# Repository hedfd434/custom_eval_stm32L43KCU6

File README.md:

# Custom evaluation board for stm32L432KCU6

This is a project of the custom evalution board for stm32L432KCU6.
The eval board was created for future test and prototypin during "2025/26 can-sat 🛰️ competition" organisated by ESA 🇪🇺 (European Space Agency), simultaneously it is a part of our PDR report 📑 (Preeliminary Desing Report).
By creating this board we want to show our capabilities in terms of electronics manufacturing ⚡📟.

<div style="display: flex; justify-content: center; gap: 20px;">
  <figure>
    
    <figcaption style="text-align: center;">Logo of my team "Crius SPACE"</figcaption>
  </figure>
  <figure>
    
    <figcaption style="text-align: center;">We are taking part in can-sat competition by ESA</figcaption>
  </figure>
</div>

<div style="display: flex; justify-content: center; gap: 20px;">
  <figure>
    
    <figcaption style="text-align: center;">Real images of soldered board (running code)</figcaption>
  </figure>
  <figure>
    
    <figcaption style="text-align: center;">Render of the board in KiCAD</figcaption>
  </figure>
</div>

## future improvements, known issues and thing which are not tested
### known issues ⚠️❗:
- missing labels  - ()

- too small package - the capacitors for the LSE (Y2) are in size of 0402, (especially during manual soldering using hot-air gun or either conventional soldering iron (0603 is ratiobale limit for the size))

- space usage - board is bigger than the most popular eval boards like "blue/black pill" ❗

### probabable issues (not tested) ⚠️❗:
- reversd ESD protection for the usb (it is not necessary to use it)

### future improvements 📈🚀:
- components - no smaller than 0603 for manual soldering

- silk layer labels - complete silk layer labels

## customisation options ⚙️🛠️:
- as you can see on the photos of the real not everything is soldered:
1. 0ohm reistor on every diode - it allows you to reduce power usage in battery base aplications 🔋🪫.

2. 0ohm resistors on signal pins for usb - allows user to use pins in 2 different ways.

3. extra user button - with pull-up resistor and place for anit-debounce capacitor.

## extra files 📂:
1. stm32l432kcu6_eval_part_list.csv - file which contains list of the used elements with quantities for 1 board.

2. documentation folder - (in progress) folder which contains documentation for every component used in the project.

3. production_file_1.zip and production_file_1 - production ready files with current version of the project

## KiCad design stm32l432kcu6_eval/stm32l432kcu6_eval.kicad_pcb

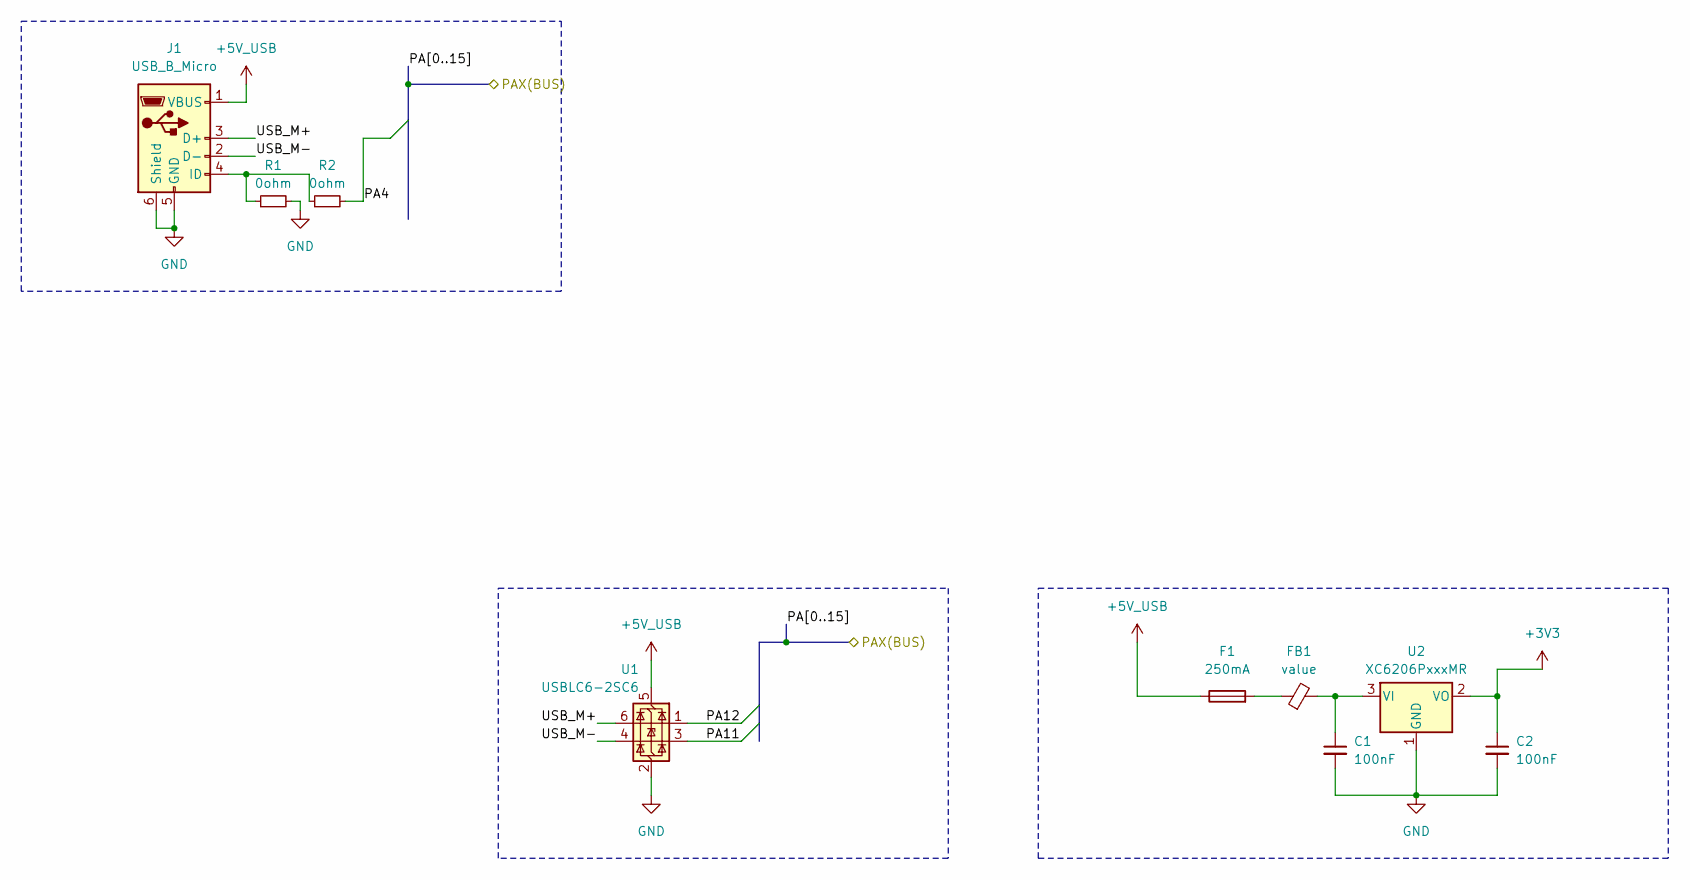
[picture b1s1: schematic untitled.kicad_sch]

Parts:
C1, C2: 100nF; C_0603_1608Metric
F1: 250mA; Fuse_0603_1608Metric
FB1: value; L_0603_1608Metric
J1: USB_B_Micro; USB_Micro-B_Molex-105017-0001
R1, R2: 0ohm; R_0603_1608Metric
U1: USBLC6-2SC6; SOT-23-6
U2: XC6206PxxxMR; SOT-23-3

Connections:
+3V3: C2.1, U2.2 (VO); also elsewhere on the board
+5V_USB: F1.1, J1.1 (VBUS), U1.5 (VBUS); also elsewhere on the board
/connectors_gpios_2_5_4/PA4: R2.2; also elsewhere on the board
/connectors_gpios_2_5_4/PA11: U1.3 (I/O2); also elsewhere on the board
/connectors_gpios_2_5_4/PA12: U1.1 (I/O1); also elsewhere on the board
/power_usb/USB_M+: J1.3 (D+), U1.6 (I/O1)
/power_usb/USB_M-: J1.2 (D-), U1.4 (I/O2)
GND: C1.2, C2.2, J1.5 (GND), J1.6 (Shield), R1.2, U1.2 (GND), U2.1 (GND); also elsewhere on the board
unnamed: F1.2, FB1.1
unnamed: J1.4 (ID), R1.1, R2.1
unnamed: C1.1, FB1.2, U2.3 (VI)

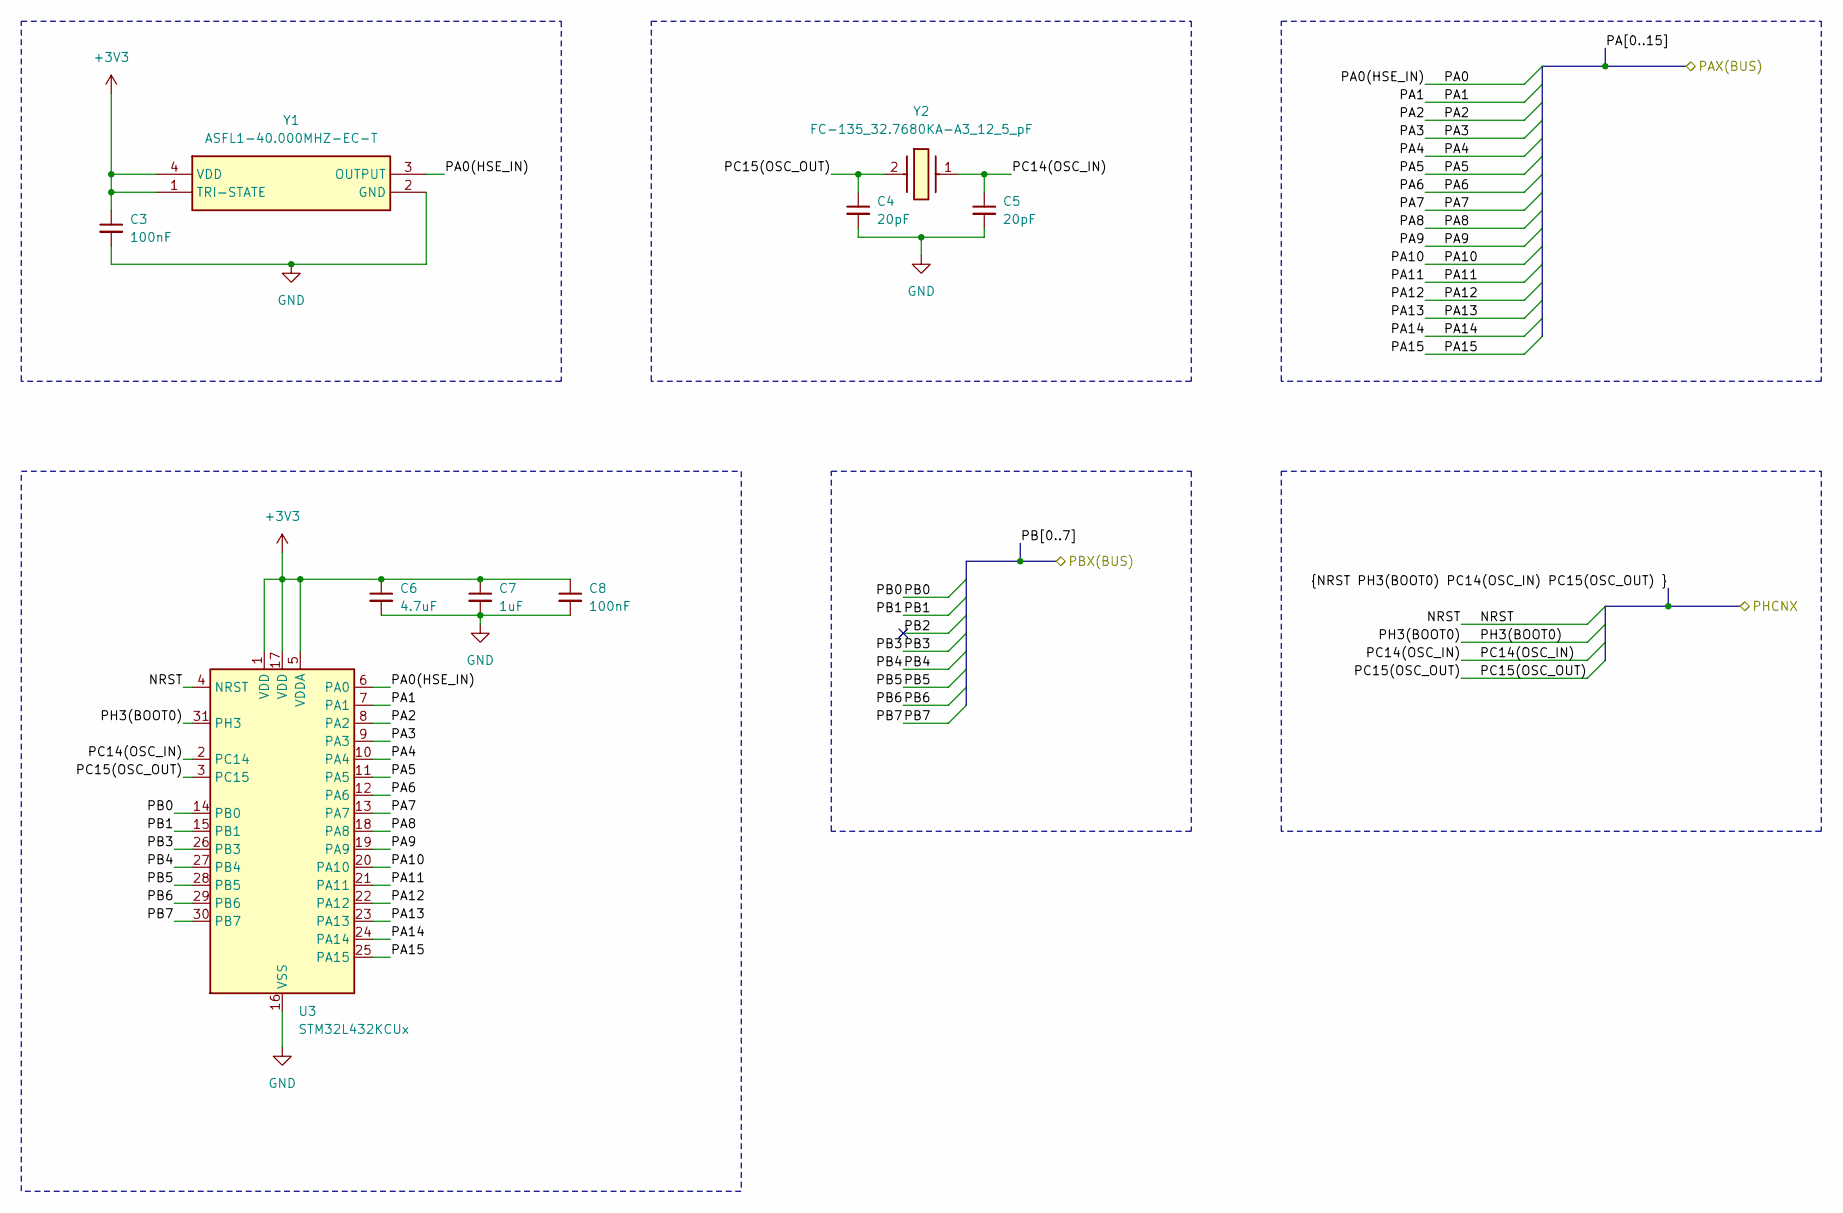
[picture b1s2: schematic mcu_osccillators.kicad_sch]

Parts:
C3, C8: 100nF; C_0603_1608Metric
C4, C5: 20pF; C_0402_1005Metric
C6: 4.7uF; C_0603_1608Metric
C7: 1uF; C_0603_1608Metric
U3: STM32L432KCUx; QFN-32-1EP_5x5mm_P0.5mm_EP3.65x3.65mm_ThermalVias
Y1: ASFL1-40.000MHZ-EC-T; ASFL1; Mouser Part Number 815-ASFL1-40.0-EC-T
Y2: FC-135_32.7680KA-A3_12_5_pF; FC-135_32_7680KA-A3; Mouser Part Number 732-FC135-32.76KAA3

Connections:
+3V3: C3.1, C6.1, C7.1, C8.1, U3.1 (VDD), U3.5 (VDDA), U3.17 (VDD), Y1.1 (TRI-STATE), Y1.4 (VDD); also elsewhere on the board
/connectors_gpios_2_5_4/NRST: U3.4 (NRST); also elsewhere on the board
/connectors_gpios_2_5_4/PA0: U3.6 (PA0), Y1.3 (OUTPUT); also elsewhere on the board
/connectors_gpios_2_5_4/PA1: U3.7 (PA1); also elsewhere on the board
/connectors_gpios_2_5_4/PA2: U3.8 (PA2); also elsewhere on the board
/connectors_gpios_2_5_4/PA3: U3.9 (PA3); also elsewhere on the board
/connectors_gpios_2_5_4/PA4: U3.10 (PA4); also elsewhere on the board
/connectors_gpios_2_5_4/PA5: U3.11 (PA5); also elsewhere on the board
/connectors_gpios_2_5_4/PA6: U3.12 (PA6); also elsewhere on the board
/connectors_gpios_2_5_4/PA7: U3.13 (PA7); also elsewhere on the board
/connectors_gpios_2_5_4/PA8: U3.18 (PA8); also elsewhere on the board
/connectors_gpios_2_5_4/PA9: U3.19 (PA9); also elsewhere on the board
/connectors_gpios_2_5_4/PA10: U3.20 (PA10); also elsewhere on the board
/connectors_gpios_2_5_4/PA11: U3.21 (PA11); also elsewhere on the board
/connectors_gpios_2_5_4/PA12: U3.22 (PA12); also elsewhere on the board
/connectors_gpios_2_5_4/PA13: U3.23 (PA13); also elsewhere on the board
/connectors_gpios_2_5_4/PA14: U3.24 (PA14); also elsewhere on the board
/connectors_gpios_2_5_4/PA15: U3.25 (PA15); also elsewhere on the board
/connectors_gpios_2_5_4/PB0: U3.14 (PB0); also elsewhere on the board
/connectors_gpios_2_5_4/PB1: U3.15 (PB1); also elsewhere on the board
/connectors_gpios_2_5_4/PB3: U3.26 (PB3); also elsewhere on the board
/connectors_gpios_2_5_4/PB4: U3.27 (PB4); also elsewhere on the board
/connectors_gpios_2_5_4/PB5: U3.28 (PB5); also elsewhere on the board
/connectors_gpios_2_5_4/PB6: U3.29 (PB6); also elsewhere on the board
/connectors_gpios_2_5_4/PB7: U3.30 (PB7); also elsewhere on the board
/connectors_gpios_2_5_4/PC14(OSC_IN): C5.1, U3.2 (PC14), Y2.1; also elsewhere on the board
/connectors_gpios_2_5_4/PC15(OSC_OUT): C4.1, U3.3 (PC15), Y2.2 (X2); also elsewhere on the board
/connectors_gpios_2_5_4/PH3(BOOT0): U3.31 (PH3); also elsewhere on the board
GND: C3.2, C4.2, C5.2, C6.2, C7.2, C8.2, U3.16 (VSS), U3.32 (VSS), U3.33 (VSS), Y1.2 (GND); also elsewhere on the board

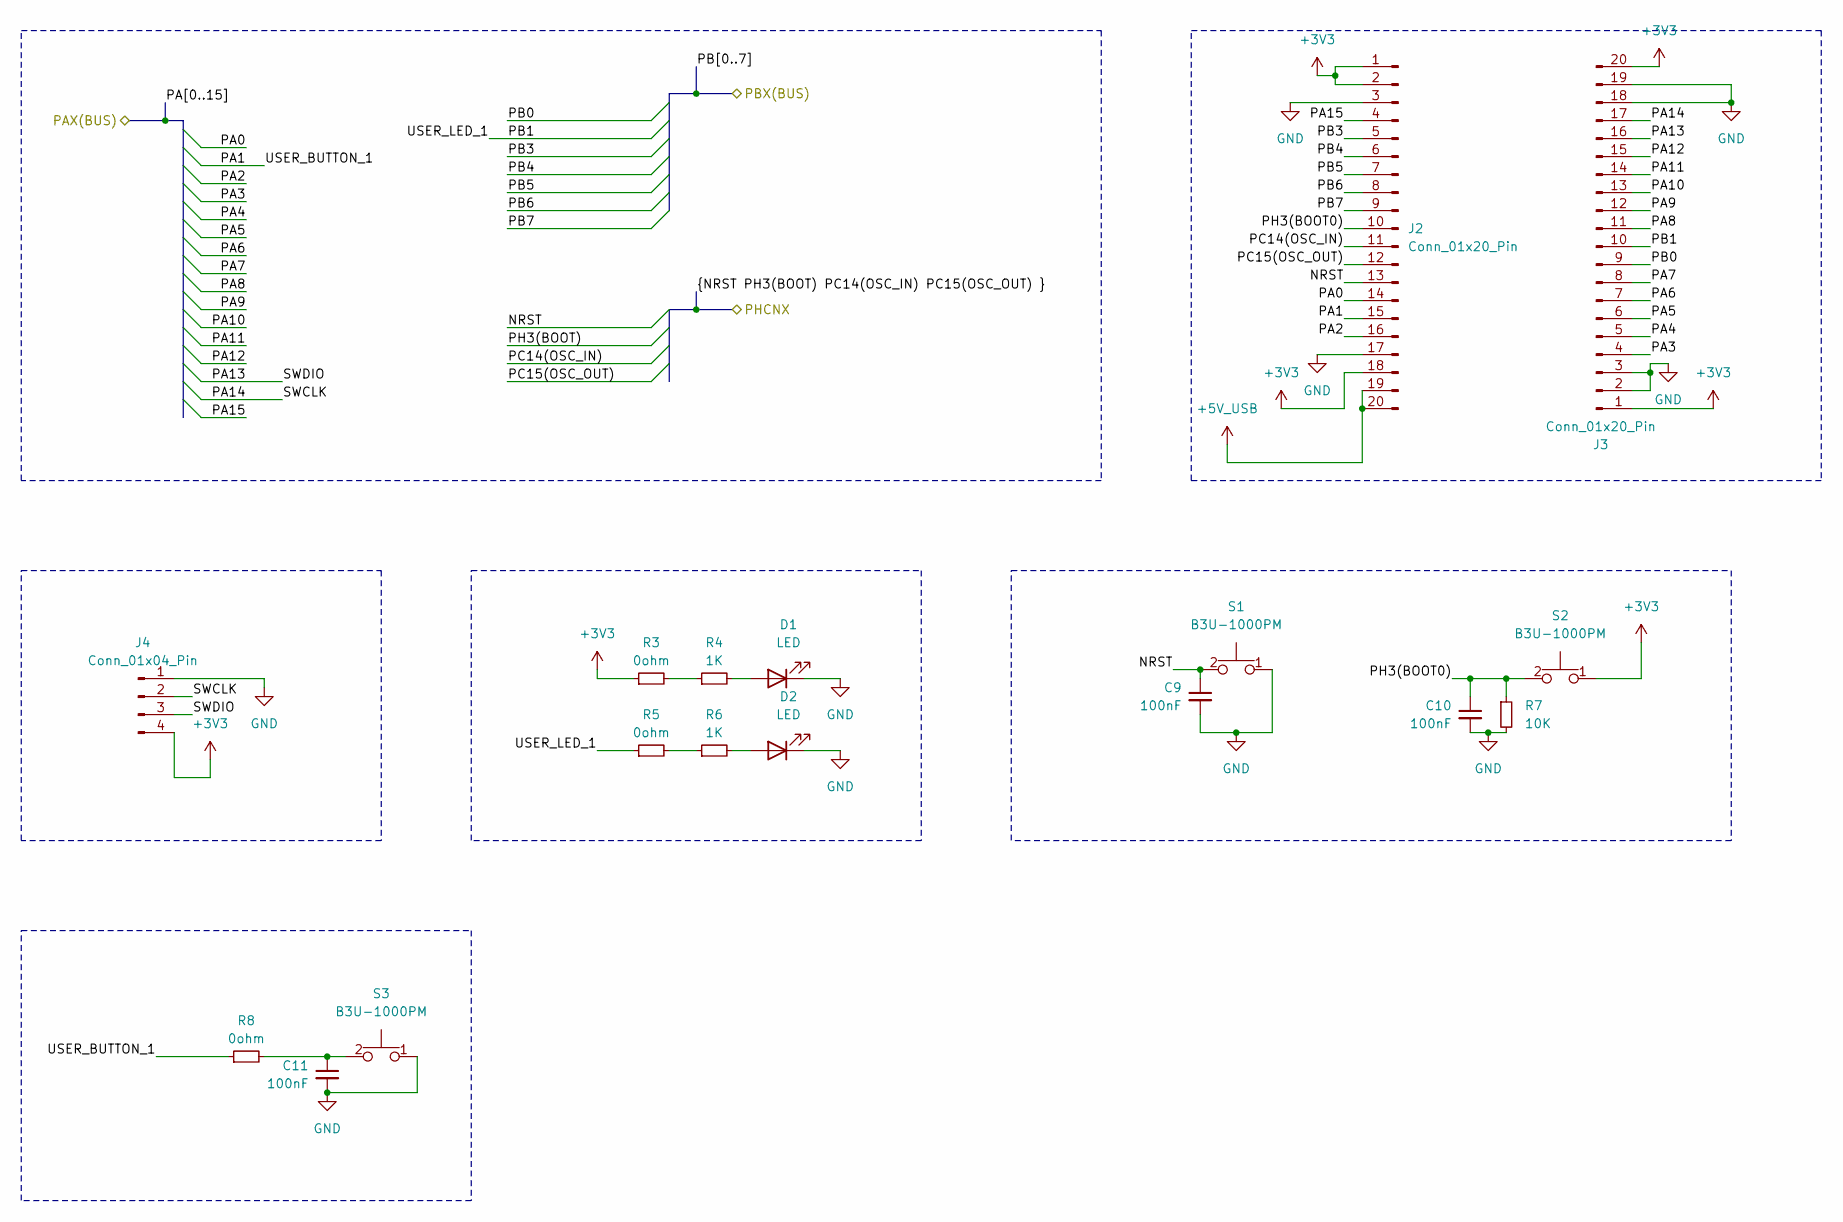
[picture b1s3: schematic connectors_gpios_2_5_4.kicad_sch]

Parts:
C9, C10, C11: 100nF; C_0603_1608Metric
D1, D2: LED; LED_0603_1608Metric
J2, J3: Conn_01x20_Pin; PinHeader_1x20_P2.54mm_Vertical
J4: Conn_01x04_Pin; PinHeader_1x04_P2.54mm_Horizontal
R3, R5, R8: 0ohm; R_0603_1608Metric
R4, R6: 1K; R_0603_1608Metric
R7: 10K; R_0603_1608Metric
S1, S2, S3: B3U-1000PM; B3U1000PM_3D_MODEL; Manufacturer_Part_Number B3U-1000PM

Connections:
+3V3: J2.1, J2.2, J2.18, J3.1, J3.20, J4.4, R3.1, S2.1; also elsewhere on the board
+5V_USB: J2.19, J2.20; also elsewhere on the board
/connectors_gpios_2_5_4/NRST: C9.1, J2.13, S1.2; also elsewhere on the board
/connectors_gpios_2_5_4/PA0: J2.14; also elsewhere on the board
/connectors_gpios_2_5_4/PA1: J2.15, R8.1; also elsewhere on the board
/connectors_gpios_2_5_4/PA2: J2.16; also elsewhere on the board
/connectors_gpios_2_5_4/PA3: J3.4; also elsewhere on the board
/connectors_gpios_2_5_4/PA4: J3.5; also elsewhere on the board
/connectors_gpios_2_5_4/PA5: J3.6; also elsewhere on the board
/connectors_gpios_2_5_4/PA6: J3.7; also elsewhere on the board
/connectors_gpios_2_5_4/PA7: J3.8; also elsewhere on the board
/connectors_gpios_2_5_4/PA8: J3.11; also elsewhere on the board
/connectors_gpios_2_5_4/PA9: J3.12; also elsewhere on the board
/connectors_gpios_2_5_4/PA10: J3.13; also elsewhere on the board
/connectors_gpios_2_5_4/PA11: J3.14; also elsewhere on the board
/connectors_gpios_2_5_4/PA12: J3.15; also elsewhere on the board
/connectors_gpios_2_5_4/PA13: J3.16, J4.3; also elsewhere on the board
/connectors_gpios_2_5_4/PA14: J3.17, J4.2; also elsewhere on the board
/connectors_gpios_2_5_4/PA15: J2.4; also elsewhere on the board
/connectors_gpios_2_5_4/PB0: J3.9; also elsewhere on the board
/connectors_gpios_2_5_4/PB1: J3.10, R5.1; also elsewhere on the board
/connectors_gpios_2_5_4/PB3: J2.5; also elsewhere on the board
/connectors_gpios_2_5_4/PB4: J2.6; also elsewhere on the board
/connectors_gpios_2_5_4/PB5: J2.7; also elsewhere on the board
/connectors_gpios_2_5_4/PB6: J2.8; also elsewhere on the board
/connectors_gpios_2_5_4/PB7: J2.9; also elsewhere on the board
/connectors_gpios_2_5_4/PC14(OSC_IN): J2.11; also elsewhere on the board
/connectors_gpios_2_5_4/PC15(OSC_OUT): J2.12; also elsewhere on the board
/connectors_gpios_2_5_4/PH3(BOOT0): C10.1, J2.10, R7.1, S2.2; also elsewhere on the board
GND: C9.2, C10.2, C11.2, D1.1 (K), D2.1 (K), J2.3, J2.17, J3.2, J3.3, J3.18, J3.19, J4.1, R7.2, S1.1, S3.1; also elsewhere on the board
unnamed: C11.1, R8.2, S3.2
unnamed: D1.2 (A), R4.2
unnamed: D2.2 (A), R6.2
unnamed: R3.2, R4.1
unnamed: R5.2, R6.1

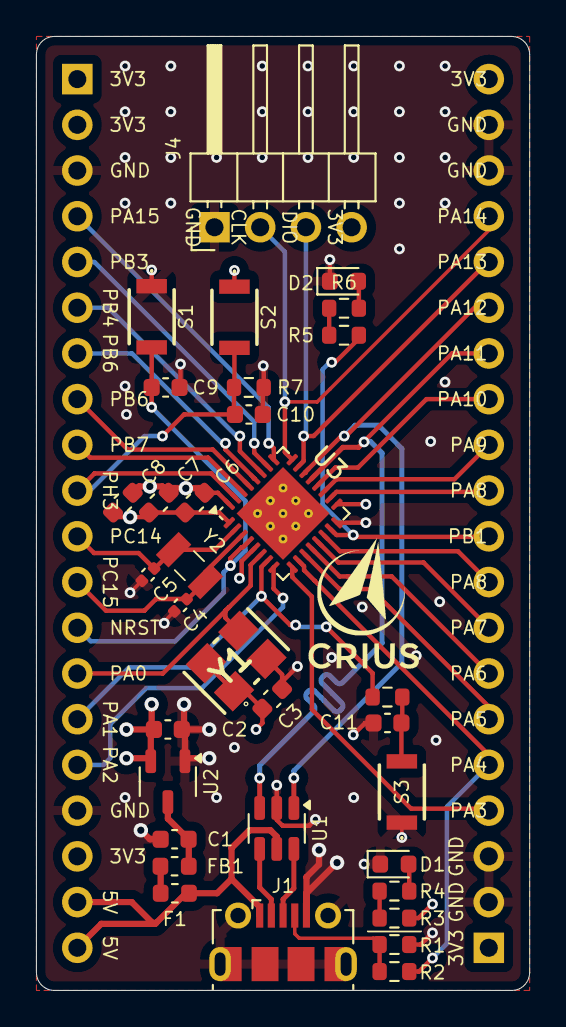
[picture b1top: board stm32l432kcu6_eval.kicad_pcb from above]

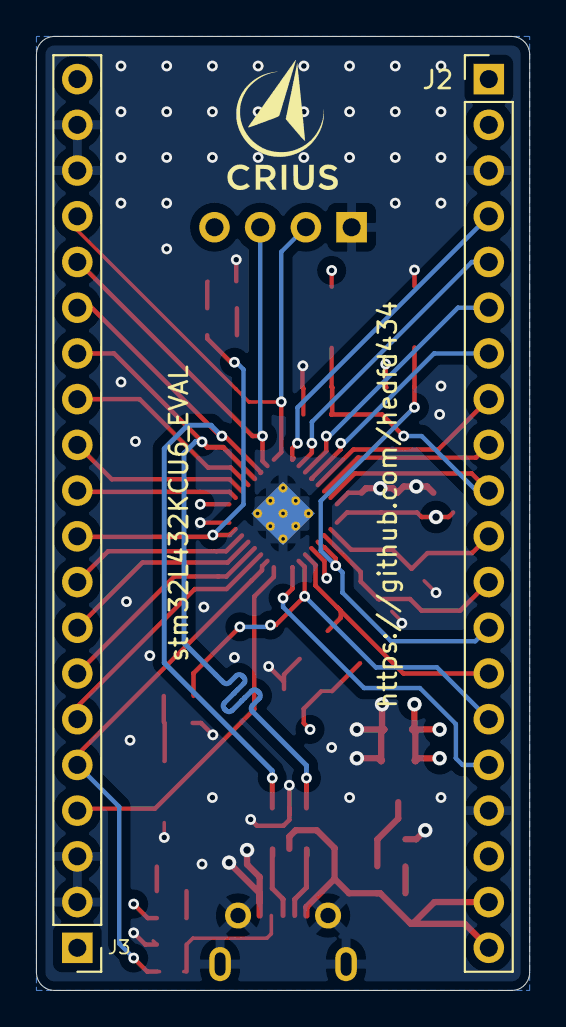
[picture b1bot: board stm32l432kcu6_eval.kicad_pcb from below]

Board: 4 copper layers, 27.4 x 53.0 mm, 35 parts (2 on the bottom side), 40 nets.

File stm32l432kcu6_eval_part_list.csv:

Reference,Value,Datasheet,Footprint,Qty,LINK
"C1,C2,C3,C8,C9,C10,C11",100nF,~,Capacitor_SMD:C_0603_1608Metric,7,https://www.tme.eu/pl/details/grm033r6ya104ke14d/kondensator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
"C4,C5",20pF,~,Capacitor_SMD:C_0402_1005Metric,2,https://www.tme.eu/pl/details/gjm1555c1h200fb01d/kondensator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
C6,4.7uF,~,Capacitor_SMD:C_0603_1608Metric,1,https://www.tme.eu/pl/details/grm188r6ya475ke15d/kondensator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
C7,1uF,~,Capacitor_SMD:C_0603_1608Metric,1,https://www.tme.eu/pl/details/gcm188r71e105ka64d/kondensator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
"D1,D2",LED,~,LED_SMD:LED_0603_1608Metric,2,null (different colours)
F1,250mA,~,Fuse:Fuse_0603_1608Metric,1,https://www.tme.eu/pl/en/details/tr-0603fa250-r/0603-smd-fus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
FB1,value,~,Inductor_SMD:L_0603_1608Metric,1,https://www.tme.eu/pl/details/blm18ba470sn1d/ferryty-koralik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
J1,USB_B_Micro,~,Connector_USB:USB_Micro-B_Molex-105017-0001,1,https://www.tme.eu/pl/en/details/mx-105017-0001/usb-ieee1394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
"J2,J3",Conn_01x20_Pin,~,Connector_PinHeader_2.54mm:PinHeader_1x20_P2.54mm_Vertical,2,null
J4,Conn_01x04_Pin,~,Connector_PinHeader_2.54mm:PinHeader_1x04_P2.54mm_Horizontal,1,null
"R1,R2,R3,R5,R8",0ohm,~,Resistor_SMD:R_0603_1608Metric,3,https://www.tme.eu/pl/details/smd0603-0r/rezystory-smd/royal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
"R4,R6",1K,~,Resistor_SMD:R_0603_1608Metric,2,https://www.tme.eu/pl/details/0201wmf1001tee/rezystory-smd/r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
R5,10K,~,Resistor_SMD:R_0603_1608Metric,1,https://www.tme.eu/pl/details/b3u-1000pm/mikroprzelaczniki-t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
"S1,S2,S3",B3U-1000PM,https://omronfs.omron.com/en_US/ecb/products/pdf/en-b3u.pdf,custom_part_library_1:B3U1000PM_3D_MODEL,3,https://www.tme.eu/pl/details/usblc6-2sc6y/diody-zabezpiecza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
U1,USBLC6-2SC6,https://www.st.com/resource/en/datasheet/usblc6-2.pdf,Package_TO_SOT_SMD:SOT-23-6,1,https://www.tme.eu/pl/en/details/usblc6-2sc6/protection-diod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
U2,XC6206PxxxMR,https://www.torexsemi.com/file/xc6206/XC6206.pdf,Package_TO_SOT_SMD:SOT-23-3,1,https://www.tme.eu/pl/details/xc6206p332mr-g/stabilizatory-n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
U3,STM32L432KCUx,https://www.st.com/resource/en/datasheet/stm32l432kc.pdf,Package_DFN_QFN:QFN-32-1EP_5x5mm_P0.5mm_EP3.65x3.65mm_ThermalVias,1,null
Y1,ASFL1-40.000MHZ-EC-T,https://abracon.com/Oscillators/ASFL1.pdf,ASFL1,1,null
Y2,FC-135_32.7680KA-A3_12_5_pF,https://support.epson.biz/td/api/doc_check.php?dl=brief_fc-1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,FC_135_CLOCK_KI_CAD:FC-135_32_7680KA-A3,1,ali (12.5pF)

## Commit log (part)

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2025-08-11 board save 1
2025-08-11 board save 2
2025-08-11 board save 3
2025-08-12 board save 4
2025-08-13 pin arragment 1
2025-08-13 organisation save 1
2025-08-13 organisation save 2
2025-08-15 project final works save 1
2025-08-15 project final works save 2
2025-08-15 project final works save 3
2025-08-16 final closing part 1
2025-08-17 elements list done 1
2025-08-17 final closing part 2 no logo
2025-08-17 final closing part 2 no logo updated excel
2025-08-17 production file 1
2025-08-17 production file 1 after review
2025-08-18 production file 1 final revisio
2025-08-18 production file 1 final revision with vias checked
2025-08-18 production file 1 final revision with vias checked save
2025-08-19 production
2025-08-19 production saves
2025-09-27 upgraded read me 1
